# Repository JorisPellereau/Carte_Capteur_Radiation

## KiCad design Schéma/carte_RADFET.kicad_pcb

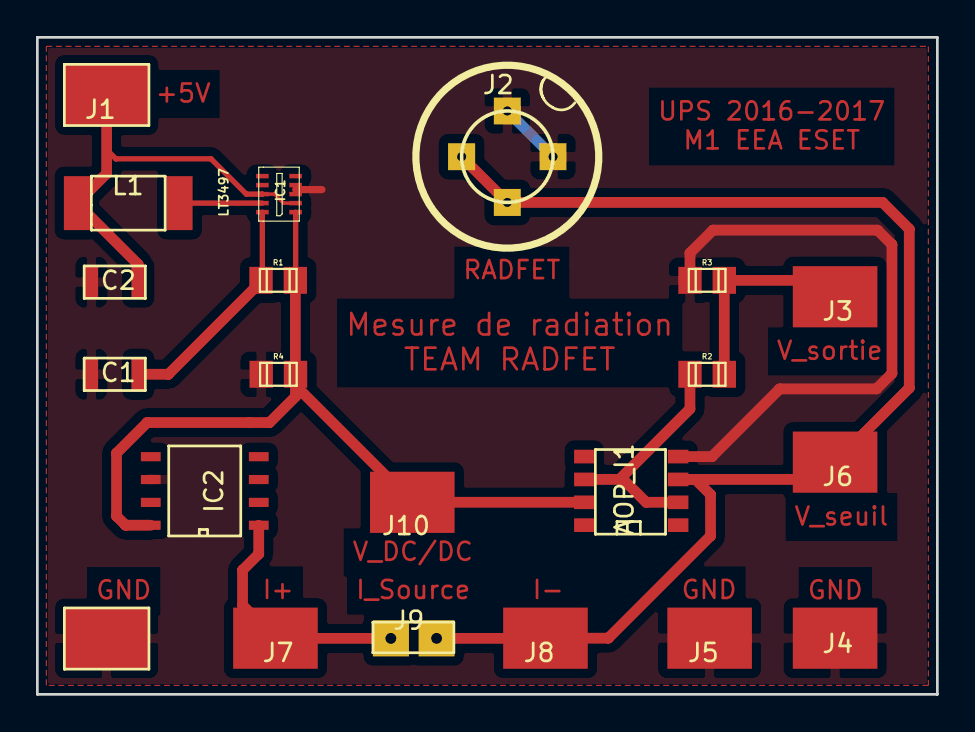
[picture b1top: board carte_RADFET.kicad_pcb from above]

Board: 2 copper layers, 50.0 x 36.5 mm, 20 parts (0 on the bottom side), 9 nets.

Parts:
AOP_I1: LT1677; S8
C1, C2: 1 uF; Capa_1µF_1206
IC1: LT3497
IC2: REF200
J1: CONN_02X01; Bornier_Alim
J2: CONN_02X02; TO5_TF53
J3, J4, J5, J6, J7, J8, J10: CONN_01X01; Pt_de_test_5016
J9: CONN_02X01; Bornier_2.54mm
L1: 15 uH; SRR6603_Series
R1: 10; r_0805
R2: 649; r_0805
R3: 100; r_0805
R4: 33k; r_0805

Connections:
+5V: C2.1, IC1.2, IC1.8, J1.1, L1.2
+32V: AOP_I1.7, IC1.1, IC2.8, J10.1, R1.1, R4.1
GND: AOP_I1.4, C1.2, C2.2, IC1.3, IC1.4, IC2.6, J1.2, J2.3, J2.4, J4.1, J5.1, R3.2, R4.2
unnamed: AOP_I1.2, AOP_I1.6, R2.2
unnamed: C1.1, IC1.10, R1.2
unnamed: IC1.9, L1.1
unnamed: IC2.1, J7.1, J9.1
unnamed: J3.1, R2.1, R3.1
Vseuil: AOP_I1.3, J2.1, J2.2, J6.1, J8.1, J9.2
